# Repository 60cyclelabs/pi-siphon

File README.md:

# pi-siphon
Simple breakout for a Pi 40-pin GPIO header, gives you tie-in points for all of the GPIO signals before passing it up to a hat.

This is a lame README so far as I'm in a rush, but I'll make it better.  For now, a picture of what you're looking at:

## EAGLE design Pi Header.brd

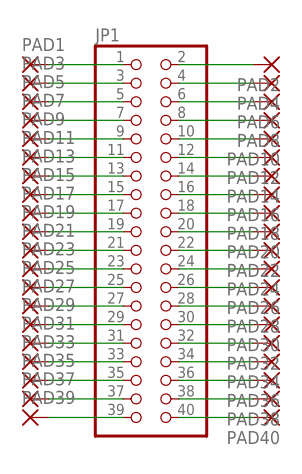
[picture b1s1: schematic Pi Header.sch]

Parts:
JP1: PINHD-2X20-BIG; 2X20-BIG
PAD1, PAD2, PAD3, PAD4, PAD5, PAD6, PAD7, PAD8, PAD9, PAD10, PAD11, PAD12, PAD13, PAD14, PAD15, PAD16, PAD17, PAD18, PAD19, PAD20, PAD21, PAD22, PAD23, PAD24, PAD25, PAD26, PAD27, PAD28, PAD29, PAD30, PAD31, PAD32, PAD33, PAD34, PAD35, PAD36, PAD37, PAD38, PAD39, PAD40: 1,6/0,8

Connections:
unnamed: JP1.1, PAD1.1
unnamed: JP1.3, PAD3.1
unnamed: JP1.5, PAD5.1
unnamed: JP1.7, PAD7.1
unnamed: JP1.9, PAD9.1
unnamed: JP1.11, PAD11.1
unnamed: JP1.13, PAD13.1
unnamed: JP1.15, PAD15.1
unnamed: JP1.17, PAD17.1
unnamed: JP1.19, PAD19.1
unnamed: JP1.21, PAD21.1
unnamed: JP1.23, PAD23.1
unnamed: JP1.25, PAD25.1
unnamed: JP1.27, PAD27.1
unnamed: JP1.29, PAD29.1
unnamed: JP1.31, PAD31.1
unnamed: JP1.33, PAD33.1
unnamed: JP1.35, PAD35.1
unnamed: JP1.37, PAD37.1
unnamed: JP1.39, PAD39.1
unnamed: JP1.40, PAD40.1
unnamed: JP1.38, PAD38.1
unnamed: JP1.36, PAD36.1
unnamed: JP1.34, PAD34.1
unnamed: JP1.32, PAD32.1
unnamed: JP1.30, PAD30.1
unnamed: JP1.28, PAD28.1
unnamed: JP1.26, PAD26.1
unnamed: JP1.24, PAD24.1
unnamed: JP1.22, PAD22.1
unnamed: JP1.20, PAD20.1
unnamed: JP1.18, PAD18.1
unnamed: JP1.16, PAD16.1
unnamed: JP1.14, PAD14.1
unnamed: JP1.12, PAD12.1
unnamed: JP1.10, PAD10.1
unnamed: JP1.8, PAD8.1
unnamed: JP1.6, PAD6.1
unnamed: JP1.4, PAD4.1
unnamed: JP1.2, PAD2.1

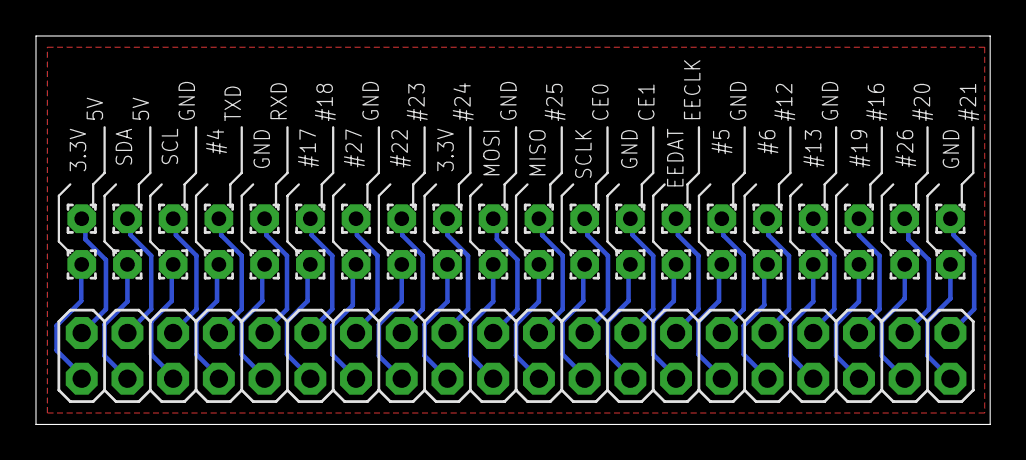
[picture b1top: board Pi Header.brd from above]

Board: 2 copper layers, 53.0 x 21.6 mm, 41 parts (0 on the bottom side), 40 nets.

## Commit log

2016-06-15 First commit of Eagle files
2016-06-15 Updated the README
2016-06-15 Again with the README
